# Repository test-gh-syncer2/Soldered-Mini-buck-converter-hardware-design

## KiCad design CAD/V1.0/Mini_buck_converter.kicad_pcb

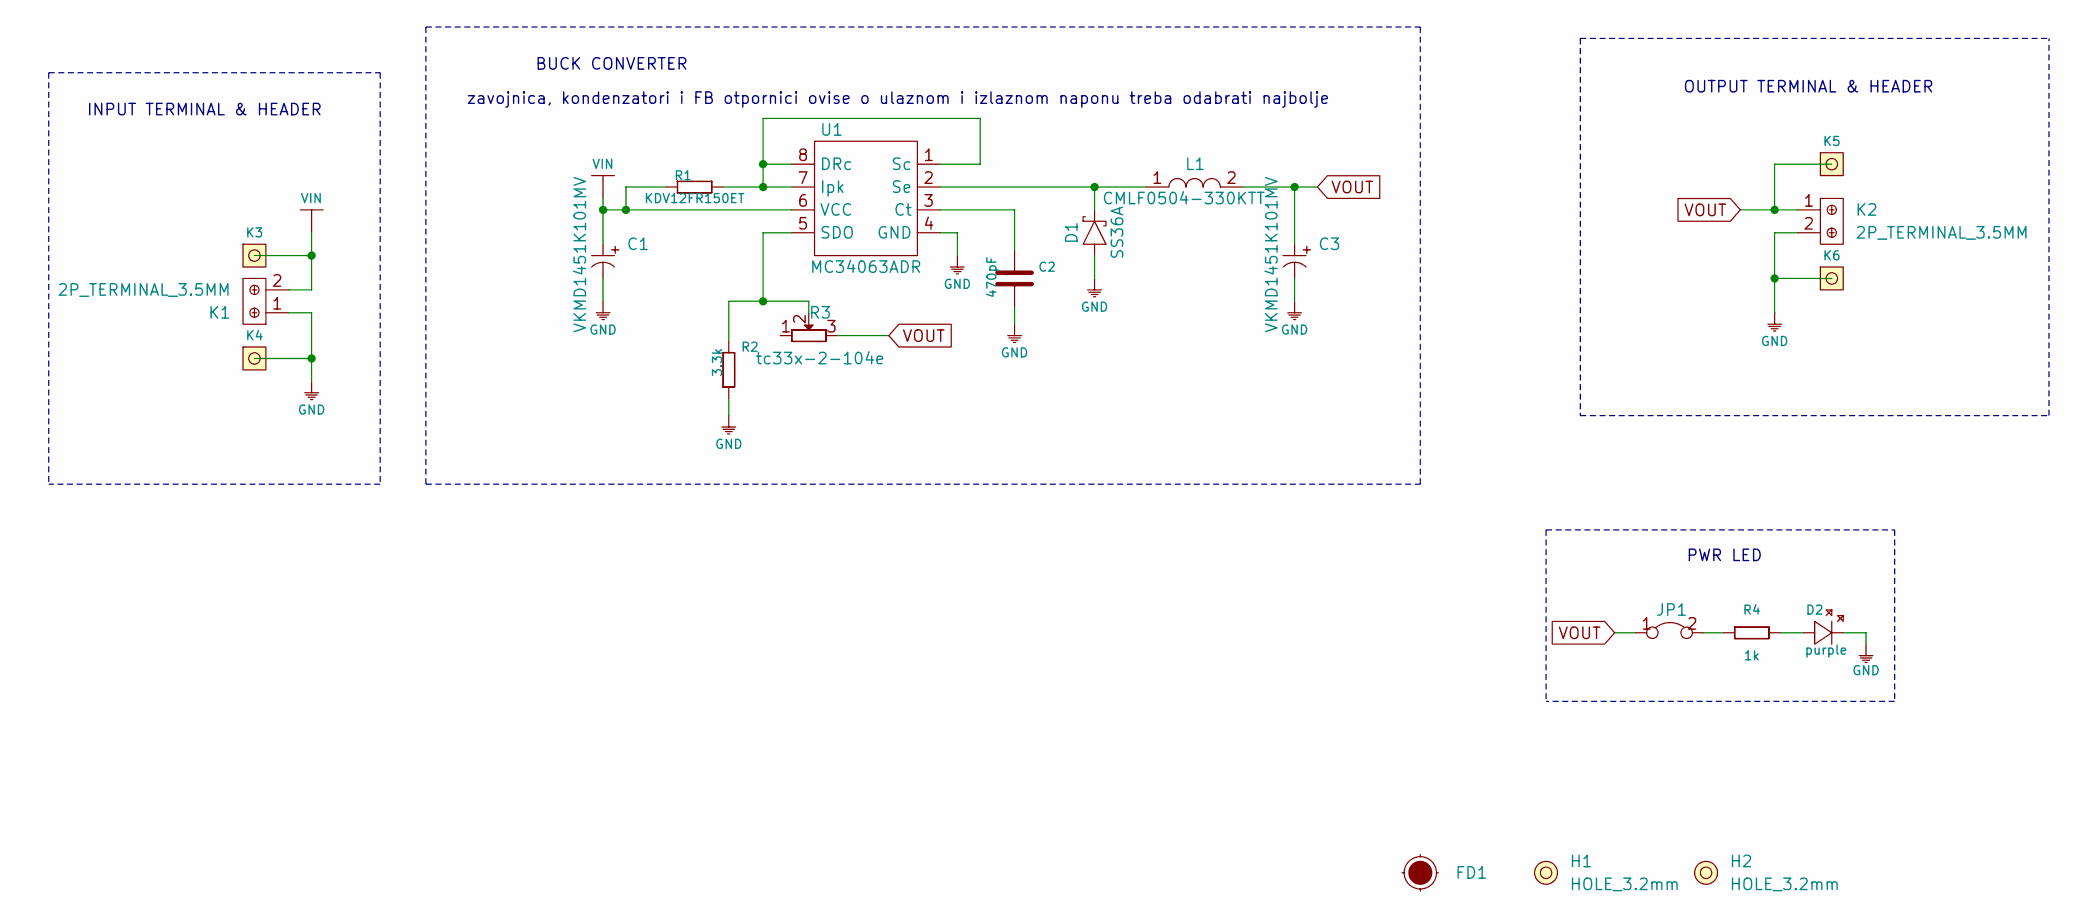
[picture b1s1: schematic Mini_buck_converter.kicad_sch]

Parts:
C1, C3: VKMD1451K101MV; ELECTROLITIC_CAP_8x8x14.5
C2: 470pF; 0603C
D1: SS36A; SMA_DIODE
D2: purple; 0402LED
FD1: Fiducial_Stencil; FIDUCIAL_1MM_PASTE
H1, H2: HOLE_3.2mm
JP1: SMD-JUMPER-CONNECTED_TRACE_NOSLODERMASK
K1, K2: 2P_TERMINAL_3.5MM
K3, K4, K5, K6: HEADER_MALE_1X1
L1: CMLF0504-330KTT
R1: KDV12FR150ET; 1206R
R2: 3.3k; 0603R
R3: tc33x-2-104e; tc33x-2-103e
R4: 1k; 0402R
U1: MC34063ADR; SOIC−8

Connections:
GND: C1.2 (-), C2.1, C3.2 (-), D1.1 (A), D2.2 (K), K1.1, K2.2, K4.1, K6.1, R2.1, U1.4 (GND)
unnamed: C2.2, U1.3 (Ct)
unnamed: D1.2 (C), L1.1, U1.2 (Se)
unnamed: D2.1 (A), R4.2
unnamed: JP1.2, R4.1
unnamed: R1.2, U1.1 (Sc), U1.7 (Ipk), U1.8 (DRc)
unnamed: R2.2, R3.2, U1.5 (SDO)
VIN: C1.1 (+), K1.2, K3.1, R1.1, U1.6 (VCC)
VOUT: C3.1 (+), JP1.1, K2.1, K5.1, L1.2, R3.3

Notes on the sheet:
INPUT TERMINAL & HEADER
zavojnica, kondenzatori i FB otpornici ovise o ulaznom i izlaznom naponu treba odabrati najbolje
BUCK CONVERTER
PWR LED
OUTPUT TERMINAL & HEADER

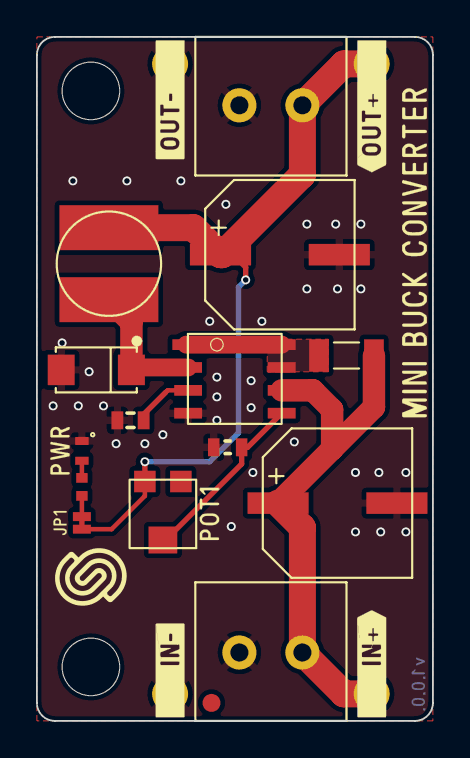
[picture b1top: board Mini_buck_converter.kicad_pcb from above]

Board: 2 copper layers, 22.0 x 38.0 mm, 21 parts (0 on the bottom side), 9 nets.

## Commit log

2021-09-23 Syncing to git
2021-09-23 Updating open source files.
